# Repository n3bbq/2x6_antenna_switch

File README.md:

# 2x6_antenna_switch
2 feedline, 6 Antenna RF Switcher plus interlock board.  From Remoteqth.com plans, but with wider RF traces.

[Mouser Parts List for Interlock board and RF board](http://www.mouser.com/ProjectManager/ProjectDetail.aspx?AccessID=e7a0b5bf58)   (v1.0.1)

Hardware Designs are under [Creative Commons Attribution-ShareAlike 4.0 International License](http://creativecommons.org/licenses/by-sa/4.0/)

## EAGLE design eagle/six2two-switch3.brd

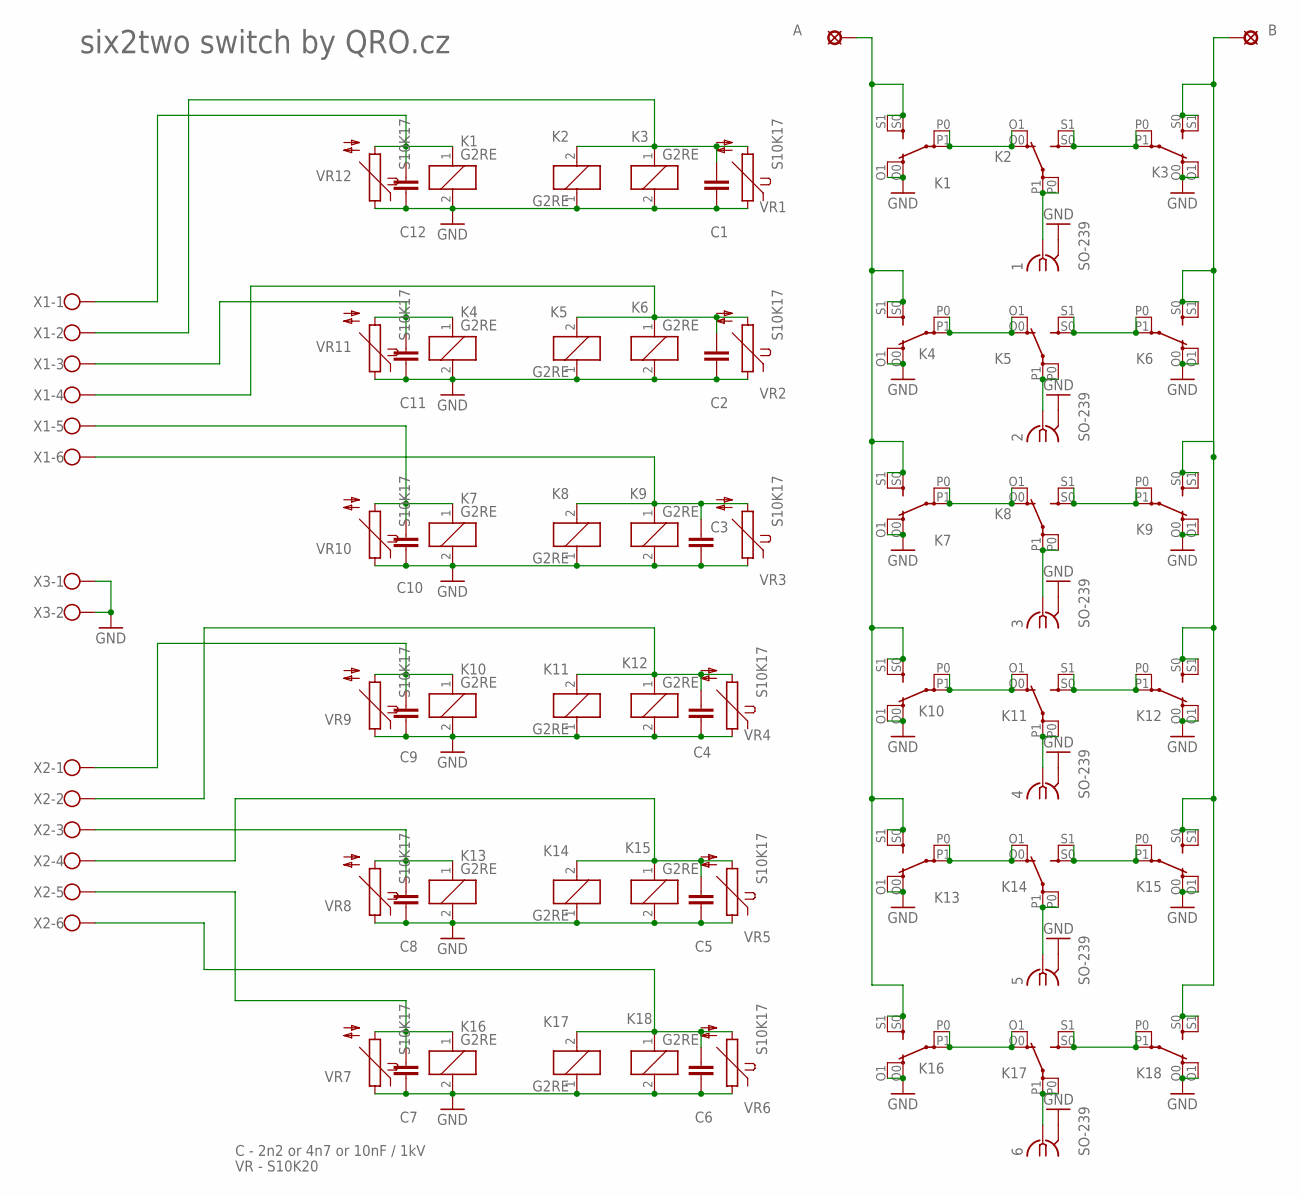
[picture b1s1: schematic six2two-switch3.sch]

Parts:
1, 2, 3, 4, 5, 6: SO-239
A: LSP13
B: LSP13
C1, C2, C3, C4, C5, C6, C7, C8, C9, C10, C11, C12: C-EU075-032X103; C075-032X103
K1, K2, K3, K4, K5, K6, K7, K8, K9, K10, K11, K12, K13, K14, K15, K16, K17, K18: G2RE
VR1, VR2, VR3, VR4, VR5, VR6, VR7, VR8, VR9, VR10, VR11, VR12: S10K17
X1, X2: W237-6
X3: W237-102

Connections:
GND: 1.P$2 (GND), 2.P$2 (GND), 3.P$2 (GND), 4.P$2 (GND), 5.P$2 (GND), 6.P$2 (GND), C1.2, C2.2, C3.2, C4.2, C5.2, C6.2, C7.2, C8.2, C9.2, C10.2, C11.2, C12.2, K1.2, K1.O0 (O), K1.O1 (O), K2.1, K3.2, K3.O0 (O), K3.O1 (O), K4.2, K4.O0 (O), K4.O1 (O), K5.1, K6.2, K6.O0 (O), K6.O1 (O), K7.2, K7.O0 (O), K7.O1 (O), K8.1, K9.2, K9.O0 (O), K9.O1 (O), K10.2, K10.O0 (O), K10.O1 (O), K11.1, K12.2, K12.O0 (O), K12.O1 (O), K13.2, K13.O0 (O), K13.O1 (O), K14.1, K15.2, K15.O0 (O), K15.O1 (O), K16.2, K16.O0 (O), K16.O1 (O), K17.1, K18.2, K18.O0 (O), K18.O1 (O), VR1.1, VR2.1, VR3.1, VR4.1, VR5.1, VR6.1, VR7.1, VR8.1, VR9.1, VR10.1, VR11.1, VR12.1, X3.1, X3.2
unnamed: K1.P0, K1.P1, K2.O0 (O), K2.O1 (O)
unnamed: K7.P0, K7.P1, K8.O0 (O), K8.O1 (O)
unnamed: K2.S0 (S), K2.S1 (S), K3.P0, K3.P1
unnamed: K4.P0, K4.P1, K5.O0 (O), K5.O1 (O)
unnamed: K5.S0 (S), K5.S1 (S), K6.P0, K6.P1
unnamed: 1.P$1 (1), K2.P0, K2.P1
unnamed: 2.P$1 (1), K5.P0, K5.P1
unnamed: K8.S0 (S), K8.S1 (S), K9.P0, K9.P1
unnamed: K10.P0, K10.P1, K11.O0 (O), K11.O1 (O)
unnamed: K11.S0 (S), K11.S1 (S), K12.P0, K12.P1
unnamed: 3.P$1 (1), K8.P0, K8.P1
unnamed: 4.P$1 (1), K11.P0, K11.P1
unnamed: K13.P0, K13.P1, K14.O0 (O), K14.O1 (O)
unnamed: K14.S0 (S), K14.S1 (S), K15.P0, K15.P1
unnamed: K16.P0, K16.P1, K17.O0 (O), K17.O1 (O)
unnamed: K17.S0 (S), K17.S1 (S), K18.P0, K18.P1
unnamed: 5.P$1 (1), K14.P0, K14.P1
unnamed: 6.P$1 (1), K17.P0, K17.P1
unnamed: A.MP, K1.S0 (S), K1.S1 (S), K4.S0 (S), K4.S1 (S), K7.S0 (S), K7.S1 (S), K10.S0 (S), K10.S1 (S), K13.S0 (S), K13.S1 (S), K16.S0 (S), K16.S1 (S)
unnamed: C1.1, K2.2, K3.1, VR1.2, X1.2
unnamed: B.MP, K3.S0 (S), K3.S1 (S), K6.S0 (S), K6.S1 (S), K9.S0 (S), K9.S1 (S), K12.S0 (S), K12.S1 (S), K15.S0 (S), K15.S1 (S), K18.S0 (S), K18.S1 (S)
unnamed: C2.1, K5.2, K6.1, VR2.2, X1.4
unnamed: C3.1, K8.2, K9.1, VR3.2, X1.6
unnamed: C4.1, K11.2, K12.1, VR4.2, X2.2
unnamed: C5.1, K14.2, K15.1, VR5.2, X2.4
unnamed: C6.1, K17.2, K18.1, VR6.2, X2.6
unnamed: C12.1, K1.1, VR12.2, X1.1
unnamed: C10.1, K7.1, VR10.2, X1.5
unnamed: C11.1, K4.1, VR11.2, X1.3
unnamed: C9.1, K10.1, VR9.2, X2.1
unnamed: C8.1, K13.1, VR8.2, X2.3
unnamed: C7.1, K16.1, VR7.2, X2.5

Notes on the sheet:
six2two switch by QRO.cz
C - 2n2 or 4n7 or 10nF / 1kV
VR - S10K20

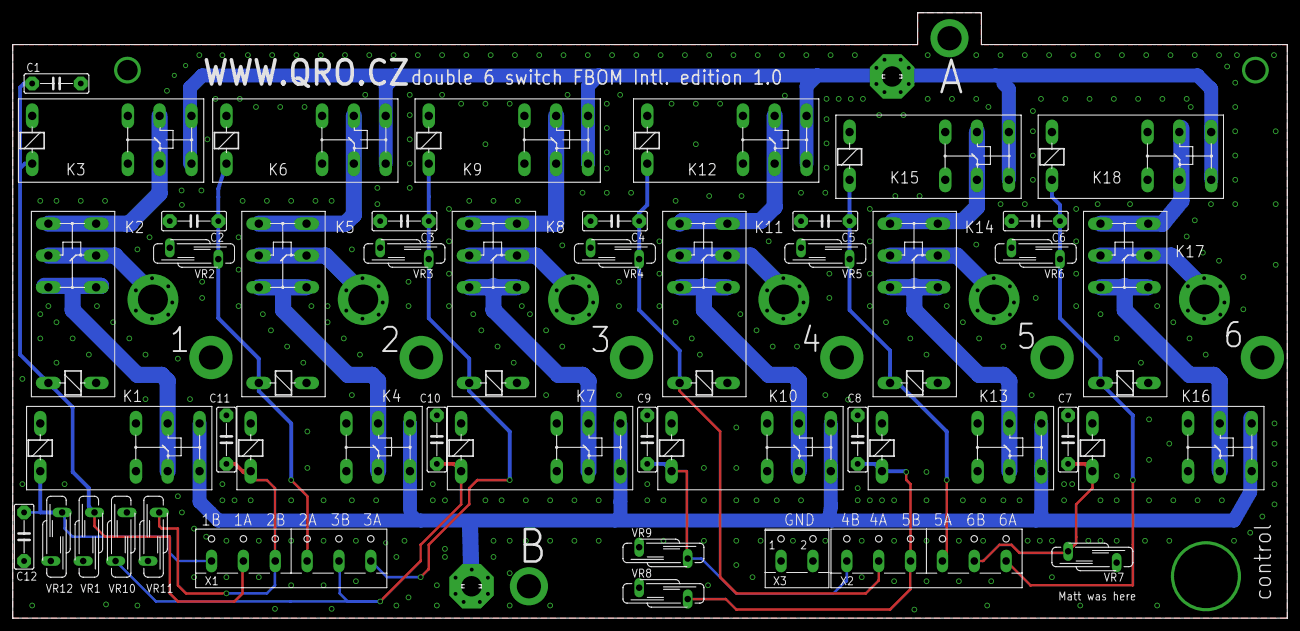
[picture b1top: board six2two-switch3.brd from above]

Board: 2 copper layers, 200.0 x 95.0 mm, 53 parts (0 on the bottom side), 33 nets.

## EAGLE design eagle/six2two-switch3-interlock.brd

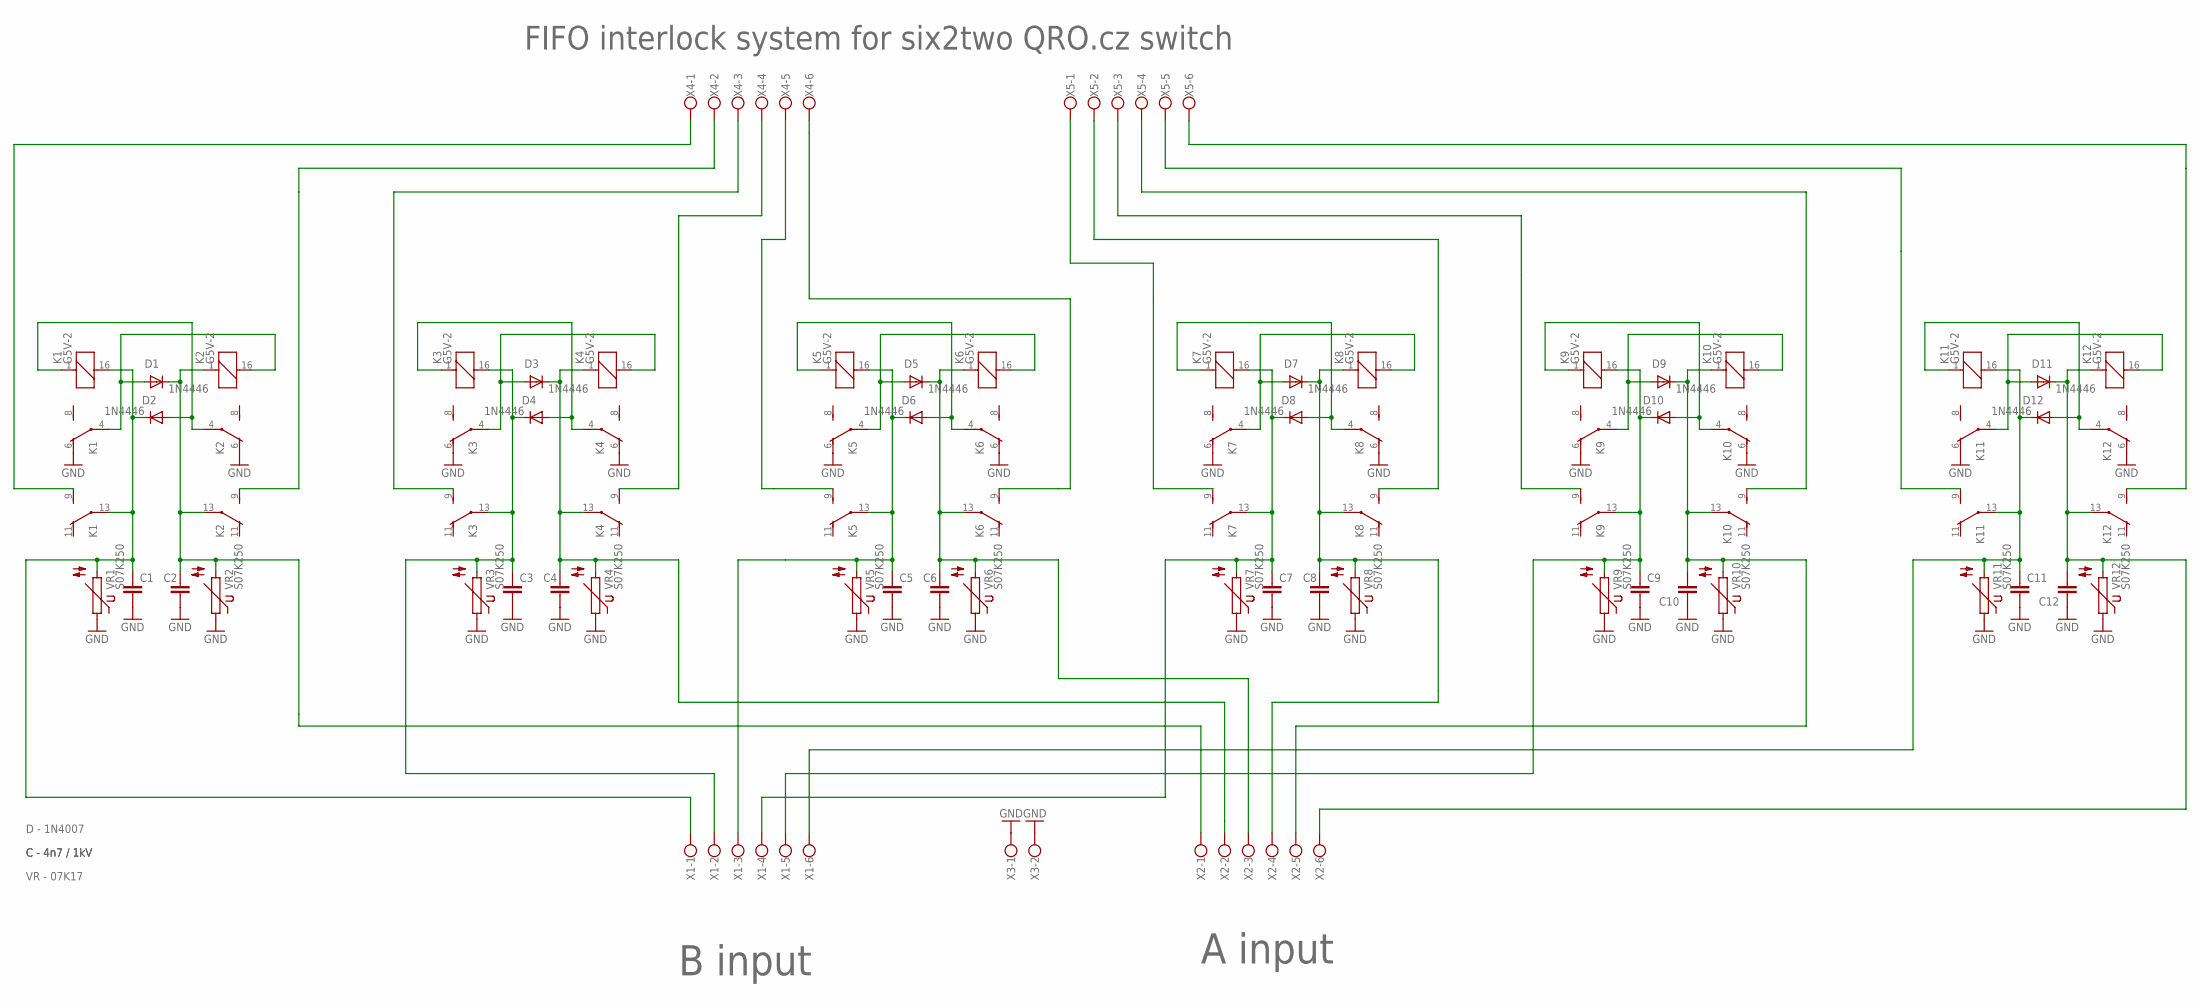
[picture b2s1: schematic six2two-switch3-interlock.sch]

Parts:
C1, C2, C3, C4, C5, C6, C7, C8, C9, C10, C11, C12: C-EU050-024X044; C050-024X044
D1, D2, D3, D4, D5, D6, D7, D8, D9, D10, D11, D12: 1N4446; DO35-10
K1, K2, K3, K4, K5, K6, K7, K8, K9, K10, K11, K12: G5V-2
VR1, VR2, VR3, VR4, VR5, VR6, VR7, VR8, VR9, VR10, VR11, VR12: S07K250
X1, X2, X4, X5: W237-136
X3: W237-102

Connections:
GND: C1.2, C2.2, C3.2, C4.2, C5.2, C6.2, C7.2, C8.2, C9.2, C10.2, C11.2, C12.2, K1.6 (O), K2.6 (O), K3.6 (O), K4.6 (O), K5.6 (O), K6.6 (O), K7.6 (O), K8.6 (O), K9.6 (O), K10.6 (O), K11.6 (O), K12.6 (O), VR1.1, VR2.1, VR3.1, VR4.1, VR5.1, VR6.1, VR7.1, VR8.1, VR9.1, VR10.1, VR11.1, VR12.1, X3.1, X3.2
unnamed: K3.9 (S), X4.3
unnamed: K1.9 (S), X4.1
unnamed: C1.1, D2.C, K1.13, K1.16 (2), VR1.2, X1.1
unnamed: C2.1, D1.C, K2.1, K2.13, VR2.2, X2.1
unnamed: D1.A, K1.4, K2.16 (2)
unnamed: D2.A, K1.1, K2.4
unnamed: K2.9 (S), X4.2
unnamed: C3.1, D4.C, K3.13, K3.16 (2), VR3.2, X1.2
unnamed: C4.1, D3.C, K4.1, K4.13, VR4.2, X2.2
unnamed: D3.A, K3.4, K4.16 (2)
unnamed: D4.A, K3.1, K4.4
unnamed: K4.9 (S), X4.4
unnamed: K5.9 (S), X4.5
unnamed: C5.1, D6.C, K5.13, K5.16 (2), VR5.2, X1.3
unnamed: C6.1, D5.C, K6.1, K6.13, VR6.2, X2.3
unnamed: D5.A, K5.4, K6.16 (2)
unnamed: D6.A, K5.1, K6.4
unnamed: K6.9 (S), X4.6
unnamed: K7.9 (S), X5.1
unnamed: C7.1, D8.C, K7.13, K7.16 (2), VR7.2, X1.4
unnamed: C8.1, D7.C, K8.1, K8.13, VR8.2, X2.4
unnamed: D7.A, K7.4, K8.16 (2)
unnamed: D8.A, K7.1, K8.4
unnamed: K8.9 (S), X5.2
unnamed: K9.9 (S), X5.3
unnamed: C9.1, D10.C, K9.13, K9.16 (2), VR9.2, X1.5
unnamed: C10.1, D9.C, K10.1, K10.13, VR10.2, X2.5
unnamed: D9.A, K9.4, K10.16 (2)
unnamed: D10.A, K9.1, K10.4
unnamed: K10.9 (S), X5.4
unnamed: K11.9 (S), X5.5
unnamed: C11.1, D12.C, K11.13, K11.16 (2), VR11.2, X1.6
unnamed: C12.1, D11.C, K12.1, K12.13, VR12.2, X2.6
unnamed: D11.A, K11.4, K12.16 (2)
unnamed: D12.A, K11.1, K12.4
unnamed: K12.9 (S), X5.6

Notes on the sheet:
A input
B input
D - 1N4007
C - 4n7 / 1kV
VR - 07K17
FIFO interlock system for six2two QRO.cz switch

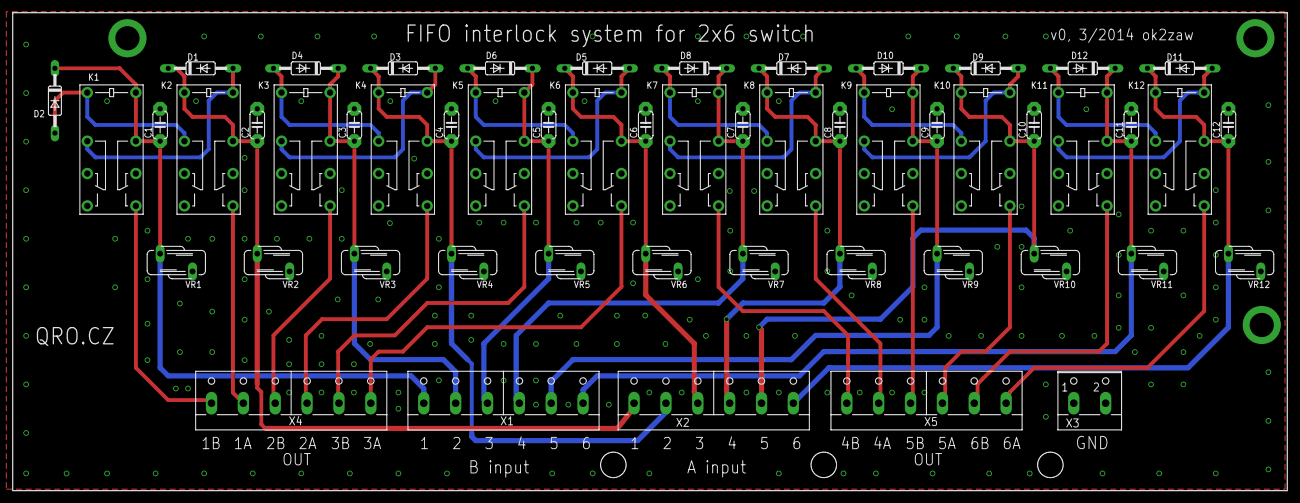
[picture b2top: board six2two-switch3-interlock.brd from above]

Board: 2 copper layers, 200.0 x 75.0 mm, 53 parts (0 on the bottom side), 37 nets.

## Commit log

2017-01-26 Initial Checkin of Antenna Switcher Plans / Schematics and Parts List.
